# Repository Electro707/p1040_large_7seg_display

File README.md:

# P1040 - Large 7-Segment Display Driver
\> PCBs (both), Rev 1
\> Firmware, WIP
\> Enclosure, WIP

This project is a driver for some large 4in 7-segment displays

# Directory Structure
- `CAD`: All FreeCAD enclosure related stuff
    - C1045: Display Holder
    - C1046: Driver Board Holder, spans 2 displays
    - C1047: Single Display Backside
    - C1048: Dowel
- E1041: PCB, Driver board, KiCAD
- E1042: PCB, Pin to Connector Adapter, KiCAD
- F1043: A demo quick firmware for testing
- F1044: Main Firmware
- `misc`: Miscellaneous files. Right now only the spreadsheet I used for some calculations exists
- `release`: Latest exported build files, includes Schematic, BOM, Gerber, and STL files

# Known Issues
> [!IMPORTANT]
> Please read the file linked below before attempting to build this hardware.

Known issues, and any workarounds, are documented in [ERRATA.md](ERRATA.md)

# Firmware
For more info on the firmware, including building and programming, see [F1044/README.md](F1044/README.md)

# License
This project is licensed under [GPLv3](LICENSE.md)**

** This excludes the files in `E1041 - PCB, Driver Board/ExternalStep`, as they came from the manufacturer.
** Also excludes the files `zones.c` and `zones.h` in `F1044`, as those are modified from the [micro_tz_d library](https://github.com/jdlambert/micro_tz_db/tree/master) which is under an MIT license

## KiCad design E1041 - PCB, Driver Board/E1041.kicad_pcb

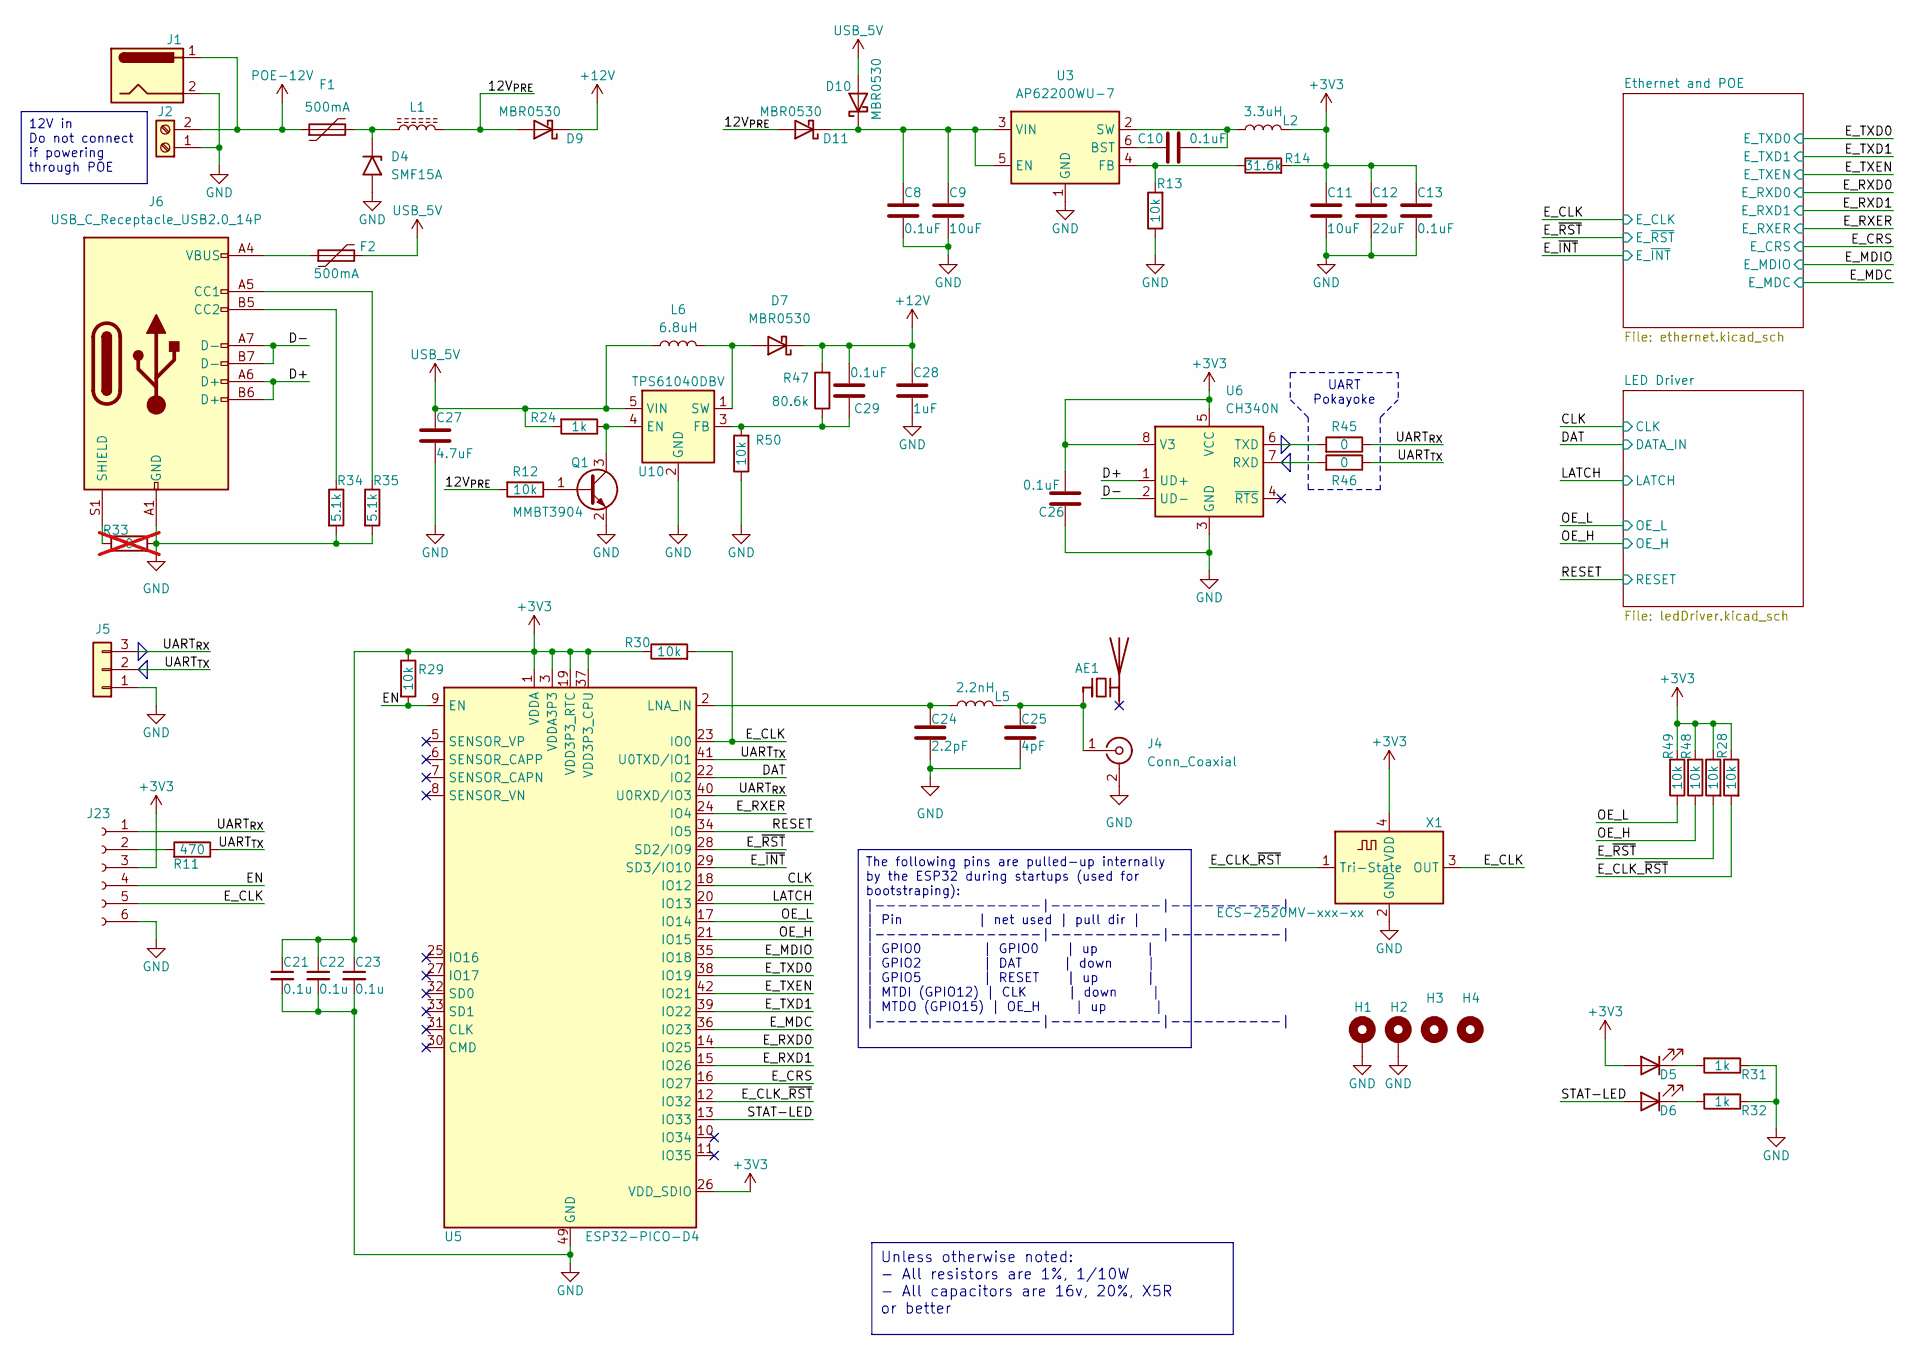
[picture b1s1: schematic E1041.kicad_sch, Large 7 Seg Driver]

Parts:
AE1: Antenna_Chip; Johanson_2450AT43F0100
C8, C10: 0.1uF; C_0805_2012Metric_Pad1.18x1.45mm_HandSolder
C9: 10uF; C_0805_2012Metric_Pad1.18x1.45mm_HandSolder
C11: 10uF; C_1206_3216Metric_Pad1.33x1.80mm_HandSolder
C12: 22uF; C_1206_3216Metric_Pad1.33x1.80mm_HandSolder
C13, C26, C29: 0.1uF; C_0805_2012Metric
C21, C22, C23: 0.1u; C_0805_2012Metric
C24: 2.2pF; C_0603_1608Metric
C25: 4pF; C_0603_1608Metric
C27: 4.7uF; C_0805_2012Metric_Pad1.18x1.45mm_HandSolder
C28: 1uF; C_0805_2012Metric_Pad1.18x1.45mm_HandSolder
D4: SMF15A; D_SMF
D5, D6: LED; LED_1206_3216Metric
D7, D9, D10, D11: MBR0530; D_SOD-123
F1, F2: 500mA; Fuse_1206_3216Metric
H1, H2: MountingHole_Pad; MountingHole_3.2mm_M3_DIN965_Pad
H3, H4: MountingHole_Pad; MountingHole_3.2mm_M3_DIN965
J1: Barrel_Jack; BarrelJack_Horizontal
J2: Screw_Terminal_01x02; TerminalBlock_Phoenix_MKDS-1,5-2-5.08_1x02_P5.08mm_Horizont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
J4: Conn_Coaxial; SMA_Amphenol_901-143_Horizontal
J5: Conn_01x03; PinSocket_1x03_P2.54mm_Vertical
J6: USB_C_Receptacle_USB2.0_14P; USB_C_Receptacle_GCT_USB4105-xx-A_16P_TopMnt_Horizontal
J23: Conn_01x06_Female; Tag-Connect_TC2030-IDC-NL_2x03_P1.27mm_Vertical
L1: L_Ferrite; L_0805_2012Metric
L2: 3.3uH; L_1206_3216Metric_Pad1.22x1.90mm_HandSolder
L5: 2.2nH; L_0603_1608Metric
L6: 6.8uH; L_1206_3216Metric_Pad1.22x1.90mm_HandSolder
Q1: MMBT3904; SOT-23
R11: 470; R_0603_1608Metric_Pad0.98x0.95mm_HandSolder
R12, R13, R29, R30, R50: 10k; R_0805_2012Metric_Pad1.20x1.40mm_HandSolder
R14: 31.6k; R_0805_2012Metric_Pad1.20x1.40mm_HandSolder
R23, R28, R48, R49: 10k; R_0805_2012Metric
R24: 1k; R_0805_2012Metric_Pad1.20x1.40mm_HandSolder
R31, R32: 1k; R_0805_2012Metric
R33: 0; R_0805_2012Metric; not fitted
R34, R35: 5.1k; R_0805_2012Metric
R45, R46: 0; R_0805_2012Metric
R47: 80.6k; R_0805_2012Metric_Pad1.20x1.40mm_HandSolder
U3: AP62200WU-7; TSOT-23-6
U5: ESP32-PICO-D4; QFN-48-1EP_7x7mm_P0.5mm_EP5.3x5.3mm
U6: CH340N; SOP-8_3.9x4.9mm_P1.27mm
U10: TPS61040DBV; SOT-23-5
X1: ECS-2520MV-xxx-xx; Oscillator_SMD_ECS_2520MV-xxx-xx-4Pin_2.5x2.0mm

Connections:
+3V3: C11.1, C12.1, C13.1, C21.1, C22.1, C23.1, C26.2, D5.2 (A), J23.3, L2.2, R14.2, R23.1, R28.1, R29.1, R30.1, R48.2, R49.2, U5.1 (VDDA), U5.3 (VDDA3P3), U5.4 (VDDA3P3), U5.19 (VDD3P3_RTC), U5.26 (VDD_SDIO), U5.37 (VDD3P3_CPU), U5.43 (VDDA), U5.46 (VDDA), U6.5 (VCC), U6.8 (V3), X1.4 (VDD); also elsewhere on the board
+12V: C28.1, C29.2, D7.1 (K), D9.1 (K), R47.2; also elsewhere on the board
/12V_{PRE}: D9.2 (A), D11.2 (A), L1.2, R12.2
/CLK: U5.18 (IO12); also elsewhere on the board
/D+: J6.A6 (D+), J6.B6 (D+), U6.1 (UD+)
/D-: J6.A7 (D-), J6.B7 (D-), U6.2 (UD-)
/DAT: U5.22 (IO2); also elsewhere on the board
/EN: J23.4, R29.2, U5.9 (EN)
/E_CLK: J23.5, R30.2, U5.23 (IO0), X1.3 (OUT); also elsewhere on the board
/E_CLK_~RST: R28.2, U5.12 (IO32), X1.1 (Tri-State)
/E_CRS: U5.16 (IO27); also elsewhere on the board
/E_MDC: U5.36 (IO23); also elsewhere on the board
/E_MDIO: U5.35 (IO18); also elsewhere on the board
/E_RXD0: U5.14 (IO25); also elsewhere on the board
/E_RXD1: U5.15 (IO26); also elsewhere on the board
/E_RXER: U5.24 (IO4); also elsewhere on the board
/E_TXD0: U5.38 (IO19); also elsewhere on the board
/E_TXD1: U5.39 (IO22); also elsewhere on the board
/E_TXEN: U5.42 (IO21); also elsewhere on the board
/E_~INT: U5.29 (SD3/IO10); also elsewhere on the board
/E_~RST: R23.2, U5.28 (SD2/IO9); also elsewhere on the board
/LATCH: U5.20 (IO13); also elsewhere on the board
/OE_H: R48.1, U5.21 (IO15); also elsewhere on the board
/OE_L: R49.1, U5.17 (IO14); also elsewhere on the board
/RESET: U5.34 (IO5); also elsewhere on the board
/STAT-LED: D6.2 (A), U5.13 (IO33)
/UART_{RX}: J5.3, J23.1, R45.1, U5.40 (U0RXD/IO3)
/UART_{TX}: J5.2, R11.1, R46.1, U5.41 (U0TXD/IO1)
GND: C8.2, C9.2, C11.2, C12.2, C13.2, C21.2, C22.2, C23.2, C24.2, C25.2, C26.1, C27.2, C28.2, D4.2 (A2), H1.1, H2.1, J1.2, J2.1, J4.2 (Ext), J5.1, J6.A1 (GND), J6.A12 (GND), J6.B1 (GND), J6.B12 (GND), J23.6, Q1.2 (E), R13.1, R31.1, R32.1, R33.2, R34.2, R35.2, R50.1, U3.1 (GND), U5.49 (GND), U6.3 (GND), U10.2 (GND), X1.2 (GND); also elsewhere on the board
unnamed: AE1.1 (FEED), C25.1, J4.1 (In), L5.2
unnamed: D4.1 (A1), F1.2, L1.1
unnamed: D5.1 (K), R31.2
unnamed: D6.1 (K), R32.2
unnamed: D7.2 (A), L6.2, U10.1 (SW)
unnamed: C8.1, C9.1, D10.1 (K), D11.1 (K), U3.3 (VIN), U3.5 (EN)
unnamed: F2.1, J6.A4 (VBUS), J6.A9 (VBUS), J6.B4 (VBUS), J6.B9 (VBUS)
unnamed: J6.A5 (CC1), R35.1
unnamed: J6.B5 (CC2), R34.1
unnamed: J6.S1 (SHIELD), R33.1
unnamed: J23.2, R11.2
unnamed: Q1.1 (B), R12.1
unnamed: Q1.3 (C), R24.1, U10.4 (EN)
unnamed: C10.1, U3.6 (BST)
unnamed: R13.2, R14.1, U3.4 (FB)
unnamed: C10.2, L2.1, U3.2 (SW)
unnamed: C24.1, L5.1, U5.2 (LNA_IN)
unnamed: R46.2, U6.7 (RXD)
unnamed: R45.2, U6.6 (TXD)
unnamed: C29.1, R47.1, R50.2, U10.3 (FB)
POE-12V: F1.1, J1.1, J2.2; also elsewhere on the board
USB_5V: C27.1, D10.2 (A), F2.2, L6.1, R24.2, U10.5 (VIN)

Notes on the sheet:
The following pins are pulled-up internally by the ESP32 during startups (used for bootstraping): |---------------|----------|----------| | Pin | net used | pull dir | |---------------|----------|----------| | GPIO0 | GPIO0 | up | | GPIO2 | DAT | down | | GPIO5 | RESET | up | | MTDI (GPIO12) | CLK 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
UART Pokayoke
12V in Do not connect if powering through POE
Unless otherwise noted: - All resistors are 1%, 1/10W - All capacitors are 16v, 20%, X5R or better

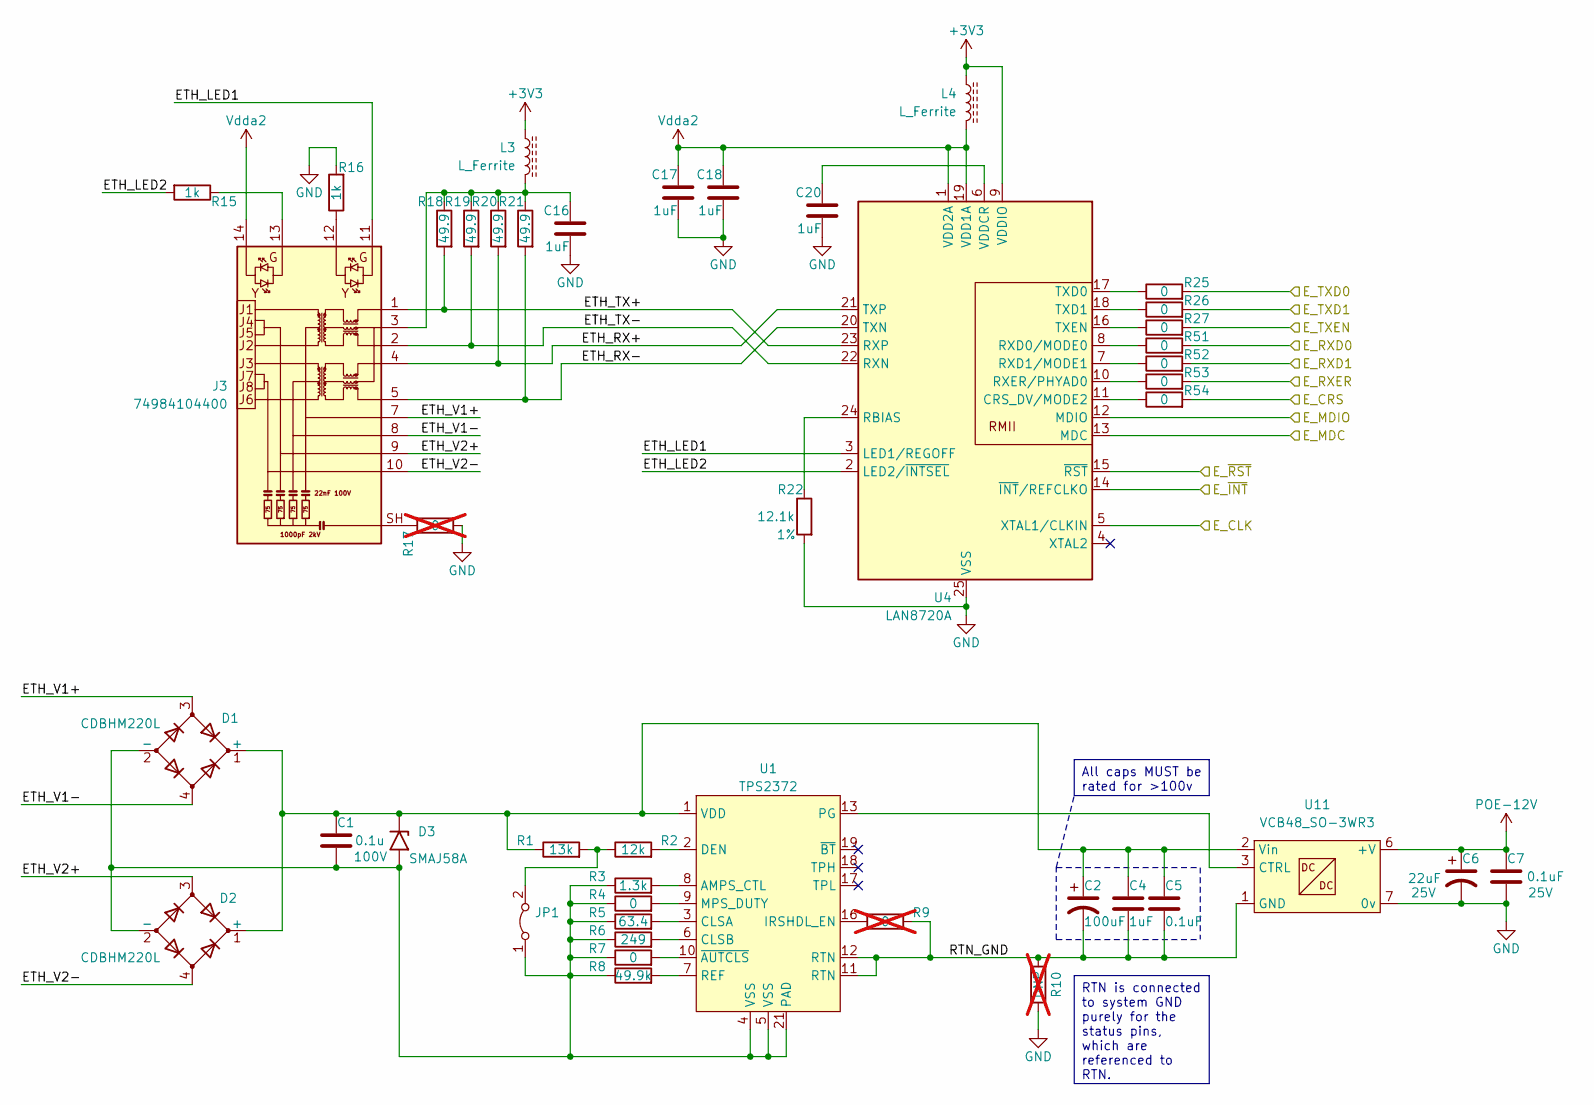
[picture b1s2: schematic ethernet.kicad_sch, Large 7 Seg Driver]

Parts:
C1: 0.1u; C_0805_2012Metric; Voltage 100V
C2: 100uF; C_Elec_6.3x5.4
C4: 1uF; C_1206_3216Metric_Pad1.33x1.80mm_HandSolder
C5: 0.1uF; C_0805_2012Metric
C6: 22uF; C_Elec_6.3x5.4; Voltage 25V
C7: 0.1uF; C_0805_2012Metric; Voltage 25V
C16, C17, C18, C20: 1uF; C_0805_2012Metric
D1, D2: CDBHM220L; TO-269AA
D3: SMAJ58A; D_SMA
J3: 74984104400
JP1: Jumper_2_Bridged; R_0805_2012Metric
L3, L4: L_Ferrite; L_0805_2012Metric
R1: 13k; R_0805_2012Metric
R2: 12k; R_0805_2012Metric
R3: 1.3k; R_0805_2012Metric
R4, R7: 0; R_0805_2012Metric
R5: 63.4; R_0805_2012Metric
R6: 249; R_0805_2012Metric
R8: 49.9k; R_0805_2012Metric
R9, R17: 0; R_0805_2012Metric; not fitted
R10: DNP; R_0805_2012Metric; not fitted
R15, R16: 1k; R_0805_2012Metric
R18, R19, R20, R21: 49.9; R_0805_2012Metric
R22: 12.1k; R_0805_2012Metric
R25, R26, R27, R51, R52, R53, R54: 0; R_0603_1608Metric
U1: TPS2372; TI_RGW0020B
U4: LAN8720A; VQFN-24-1EP_4x4mm_P0.5mm_EP2.5x2.5mm_ThermalVias
U11: VCB48_SO-3WR3

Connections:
+3V3: L3.2, L4.2, U4.9 (VDDIO); also elsewhere on the board
/E_CLK: U4.5 (XTAL1/CLKIN); also elsewhere on the board
/E_CRS: R54.2; also elsewhere on the board
/E_MDC: U4.13 (MDC); also elsewhere on the board
/E_MDIO: U4.12 (MDIO); also elsewhere on the board
/E_RXD0: R51.2; also elsewhere on the board
/E_RXD1: R52.2; also elsewhere on the board
/E_RXER: R53.2; also elsewhere on the board
/E_TXD0: R25.2; also elsewhere on the board
/E_TXD1: R26.2; also elsewhere on the board
/E_TXEN: R27.2; also elsewhere on the board
/E_~INT: U4.14 (~INT/REFCLKO); also elsewhere on the board
/E_~RST: U4.15 (~RST); also elsewhere on the board
/Ethernet and POE/ETH_LED1: J3.11, U4.3 (LED1/REGOFF)
/Ethernet and POE/ETH_LED2: R15.2, U4.2 (LED2/~INTSEL)
/Ethernet and POE/ETH_RX+: J3.4 (RD+), R20.2, U4.21 (TXP)
/Ethernet and POE/ETH_RX-: J3.5 (RD-), R21.2, U4.20 (TXN)
/Ethernet and POE/ETH_TX+: J3.1 (TD+), R18.2, U4.23 (RXP)
/Ethernet and POE/ETH_TX-: J3.2 (TD-), R19.2, U4.22 (RXN)
/Ethernet and POE/ETH_V1+: D1.3, J3.7 (V1+)
/Ethernet and POE/ETH_V1-: D1.4, J3.8 (V1-)
/Ethernet and POE/ETH_V2+: D2.3, J3.9 (V2+)
/Ethernet and POE/ETH_V2-: D2.4, J3.10 (V2-)
/Ethernet and POE/RTN_GND: C2.2, C4.2, C5.2, R9.2, R10.2, U1.11 (RTN), U1.12 (RTN), U11.1 (GND)
GND: C6.2, C7.2, C16.2, C17.2, C18.2, C20.2, R10.1, R16.2, R17.2, R22.2, U4.25 (VSS), U11.7 (0v); also elsewhere on the board
unnamed: C1.1, C2.1, C4.1, C5.1, D1.1 (+), D2.1 (+), D3.1 (A1), R1.1, U1.1 (VDD), U11.2 (Vin)
unnamed: C1.2, D1.2 (-), D2.2 (-), D3.2 (A2), JP1.1 (A), R3.1, R4.1, R5.1, R6.1, R7.1, R8.1, U1.4 (VSS), U1.5 (VSS), U1.21 (PAD)
unnamed: C16.1, J3.3 (CD), L3.1, R18.1, R19.1, R20.1, R21.1
unnamed: J3.12, R16.1
unnamed: J3.13, R15.1
unnamed: J3.SH, R17.1
unnamed: JP1.2 (B), R1.2, R2.1
unnamed: R3.2, U1.8 (AMPS_CTL)
unnamed: R5.2, U1.3 (CLSA)
unnamed: R6.2, U1.6 (CLSB)
unnamed: R2.2, U1.2 (DEN)
unnamed: R9.1, U1.16 (IRSHDL_EN)
unnamed: R4.2, U1.9 (MPS_DUTY)
unnamed: U1.13 (PG), U11.3 (CTRL)
unnamed: R8.2, U1.7 (REF)
unnamed: R7.2, U1.10 (~AUTCLS)
unnamed: R54.1, U4.11 (CRS_DV/MODE2)
unnamed: R22.1, U4.24 (RBIAS)
unnamed: R51.1, U4.8 (RXD0/MODE0)
unnamed: R52.1, U4.7 (RXD1/MODE1)
unnamed: R53.1, U4.10 (RXER/PHYAD0)
unnamed: R25.1, U4.17 (TXD0)
unnamed: R26.1, U4.18 (TXD1)
unnamed: R27.1, U4.16 (TXEN)
unnamed: C20.1, U4.6 (VDDCR)
POE-12V: C6.1, C7.1, U11.6 (+V); also elsewhere on the board
Vdda2: C17.1, C18.1, J3.14, L4.1, U4.1 (VDD2A), U4.19 (VDD1A)

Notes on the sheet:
RTN is connected to system GND purely for the status pins, which are referenced to RTN.
All caps MUST be rated for >100v

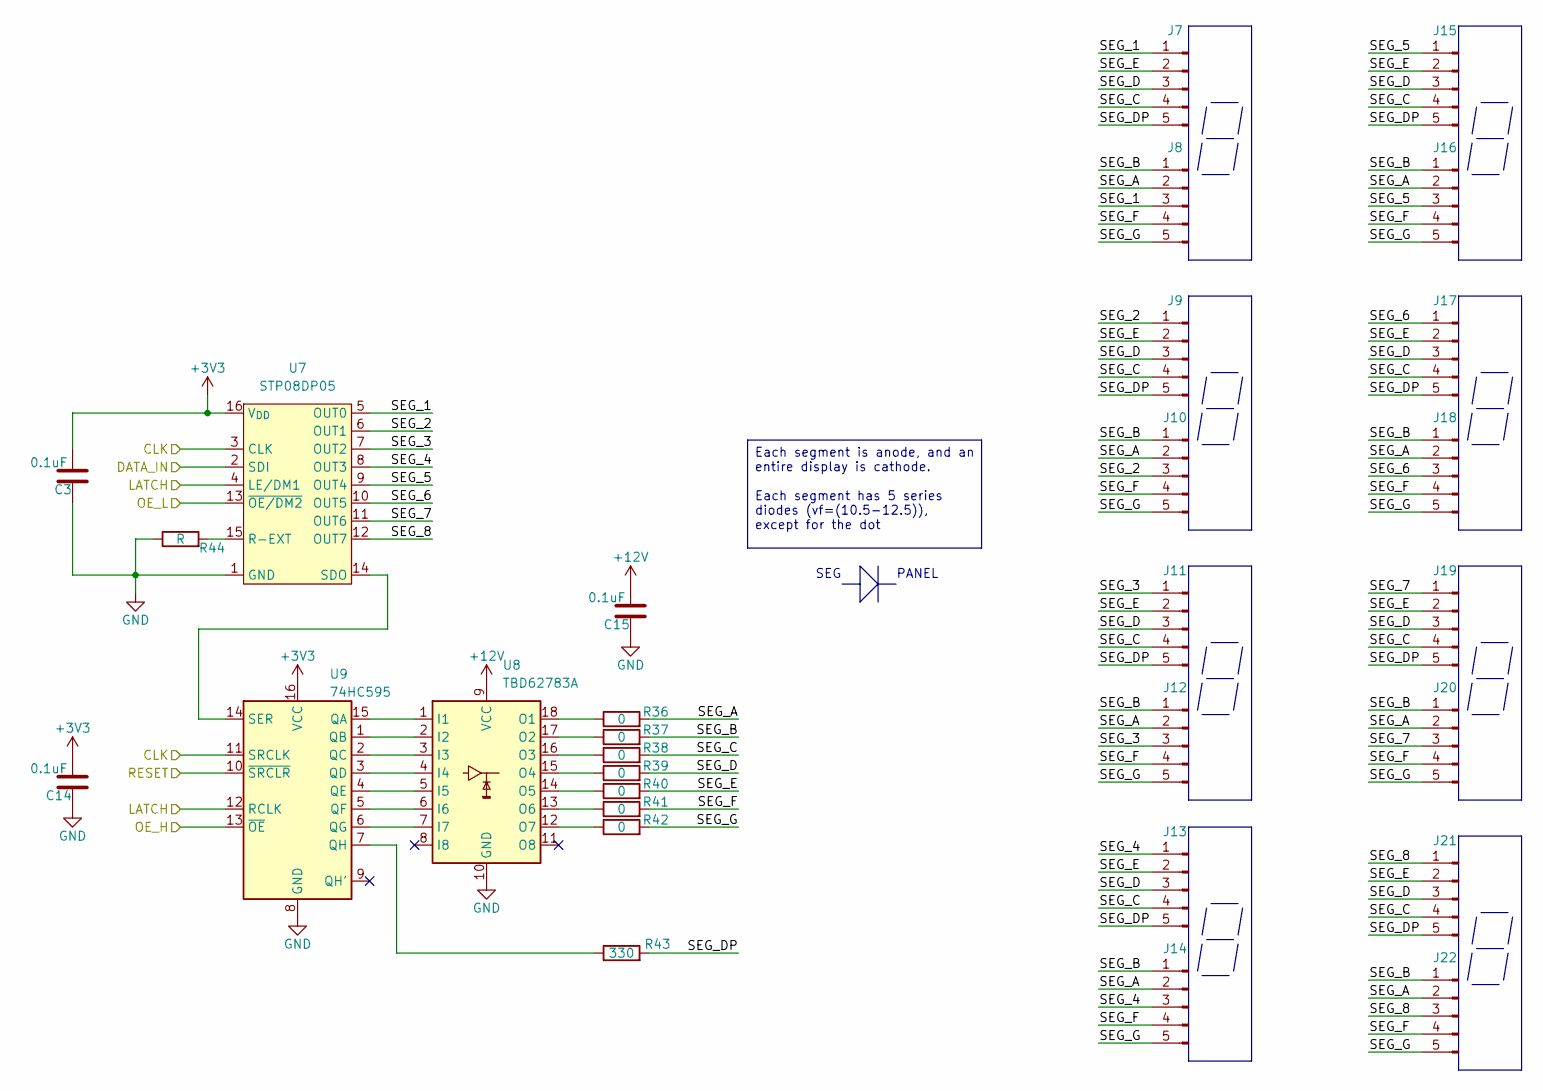
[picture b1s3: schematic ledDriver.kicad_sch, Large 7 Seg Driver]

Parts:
C3, C14, C15: 0.1uF; C_0805_2012Metric
J7, J8, J9, J10, J11, J12, J13, J14, J15, J16, J17, J18, J19, J20, J21, J22: Conn_01x05_Pin; JST_PH_B5B-PH-K_1x05_P2.00mm_Vertical
R36, R37, R38, R39, R40, R41, R42: 0; R_0805_2012Metric
R43: 330; R_0805_2012Metric
R44: R; R_0805_2012Metric
U7: STP08DP05; SO-16_3.9x9.9mm_P1.27mm
U8: TBD62783A; SOP-18_7x12.5mm_P1.27mm
U9: 74HC595; SO-16_3.9x9.9mm_P1.27mm

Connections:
+3V3: C3.2, C14.2, U7.16 (V_{DD}), U9.16 (VCC); also elsewhere on the board
+12V: C15.2, U8.9 (VCC); also elsewhere on the board
/CLK: U7.3 (CLK), U9.11 (SRCLK); also elsewhere on the board
/DAT: U7.2 (SDI); also elsewhere on the board
/LATCH: U7.4 (LE/DM1), U9.12 (RCLK); also elsewhere on the board
/LED Driver/SEG_1: J7.1, J8.3, U7.5 (OUT0)
/LED Driver/SEG_2: J9.1, J10.3, U7.6 (OUT1)
/LED Driver/SEG_3: J11.1, J12.3, U7.7 (OUT2)
/LED Driver/SEG_4: J13.1, J14.3, U7.8 (OUT3)
/LED Driver/SEG_5: J15.1, J16.3, U7.9 (OUT4)
/LED Driver/SEG_6: J17.1, J18.3, U7.10 (OUT5)
/LED Driver/SEG_7: J19.1, J20.3, U7.11 (OUT6)
/LED Driver/SEG_8: J21.1, J22.3, U7.12 (OUT7)
/LED Driver/SEG_A: J8.2, J10.2, J12.2, J14.2, J16.2, J18.2, J20.2, J22.2, R36.2
/LED Driver/SEG_B: J8.1, J10.1, J12.1, J14.1, J16.1, J18.1, J20.1, J22.1, R37.2
/LED Driver/SEG_C: J7.4, J9.4, J11.4, J13.4, J15.4, J17.4, J19.4, J21.4, R38.2
/LED Driver/SEG_D: J7.3, J9.3, J11.3, J13.3, J15.3, J17.3, J19.3, J21.3, R39.2
/LED Driver/SEG_DP: J7.5, J9.5, J11.5, J13.5, J15.5, J17.5, J19.5, J21.5, R43.2
/LED Driver/SEG_E: J7.2, J9.2, J11.2, J13.2, J15.2, J17.2, J19.2, J21.2, R40.2
/LED Driver/SEG_F: J8.4, J10.4, J12.4, J14.4, J16.4, J18.4, J20.4, J22.4, R41.2
/LED Driver/SEG_G: J8.5, J10.5, J12.5, J14.5, J16.5, J18.5, J20.5, J22.5, R42.2
/OE_H: U9.13 (~OE); also elsewhere on the board
/OE_L: U7.13 (~OE/DM2); also elsewhere on the board
/RESET: U9.10 (~SRCLR); also elsewhere on the board
GND: C3.1, C14.1, C15.1, R44.1, U7.1 (GND), U8.10 (GND), U9.8 (GND); also elsewhere on the board
unnamed: R44.2, U7.15 (R-EXT)
unnamed: U7.14 (SDO), U9.14 (SER)
unnamed: U8.1 (I1), U9.15 (QA)
unnamed: U8.2 (I2), U9.1 (QB)
unnamed: U8.3 (I3), U9.2 (QC)
unnamed: U8.4 (I4), U9.3 (QD)
unnamed: U8.5 (I5), U9.4 (QE)
unnamed: U8.6 (I6), U9.5 (QF)
unnamed: U8.7 (I7), U9.6 (QG)
unnamed: R36.1, U8.18 (O1)
unnamed: R37.1, U8.17 (O2)
unnamed: R38.1, U8.16 (O3)
unnamed: R39.1, U8.15 (O4)
unnamed: R40.1, U8.14 (O5)
unnamed: R41.1, U8.13 (O6)
unnamed: R42.1, U8.12 (O7)
unnamed: R43.1, U9.7 (QH)

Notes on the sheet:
SEG
PANEL
Each segment is anode, and an entire display is cathode. Each segment has 5 series diodes (vf=(10.5-12.5)), except for the dot

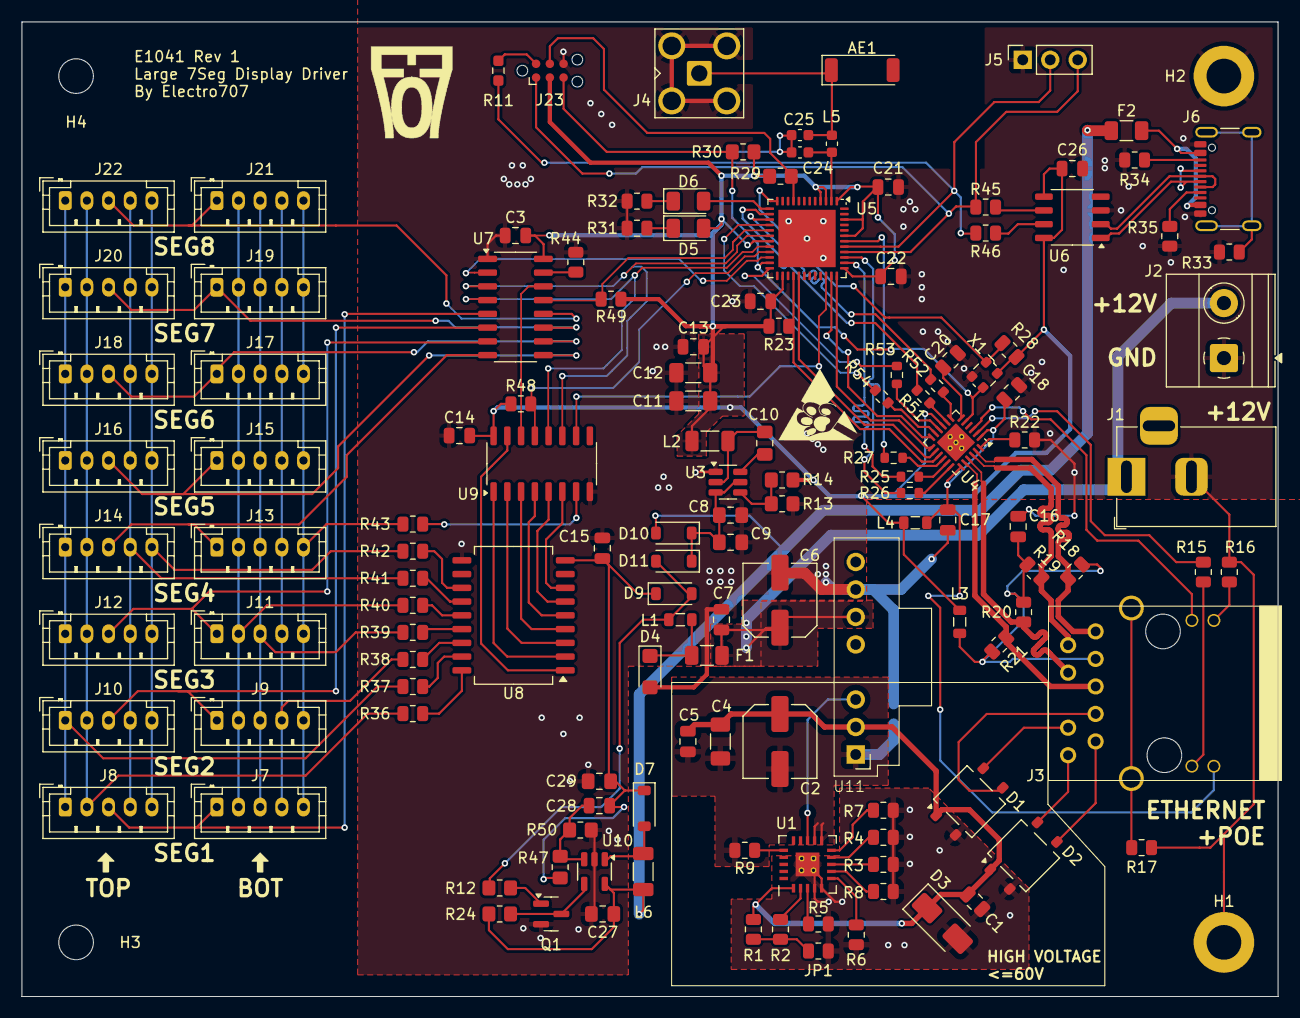
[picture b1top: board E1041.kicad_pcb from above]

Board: 2 copper layers, 116.0 x 90.0 mm, 141 parts (1 on the bottom side), 121 nets.

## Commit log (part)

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2025-08-24 Initial Commit, added PCB files to tag and lock in
2025-08-25 Added CAD stuff
2025-08-25 Added firmware stuff
2025-08-25 Added errata images
2025-09-16 Modified the case a bit
2025-09-20 c1047 rev 3
2025-09-21 Updates to firmware, should be mostly good except for niche features
2025-09-21 Some doc updates
2025-10-07 more work on firmware
2025-11-09 new model
2026-01-05 Updated BOM, and errata for typo
2026-01-05 Updated for dowel pin...I think
2026-01-05 Added 'Part Number' in schematic, no design change
